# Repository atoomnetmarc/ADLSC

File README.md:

# ADLSC, Atoomnet's Digital Led String Controller

ESP32 based 5V digital LED controller build for use with [WLED](https://kno.wled.ge/).

# Design choices

The chosen ESP32 classic is the ESP32-WROVER-E with PSRAM on a [ESP32-DevKitC V4 board](https://docs.espressif.com/projects/esp-idf/en/release-v4.2/esp32/hw-reference/esp32/get-started-devkitc.html).

The ESP32 must be able to control the power to the LEDs. That means a high-side power switch.

The ESP32 will be powered by the same 5V power supply. A 0.5A 1812 polyfuse with 5V bidirectional TVS diode will used to protect the low power electronics.

5V will be monitored by a MAX809M reset ic. When the power supply voltage is too low the ESP32 will be turned off and in turn the LEDs will be turned off.

A N-channel MOSFET (AOD442) will be used as a 5V reverse polarity protection.

The power to the LEDs can be injected in 2 sections. Both are fused by a 5x20mm slow blow glass fuse paired with 5V bidirectional TVS diodes (like SMBJ5.0CA). Red LEDs will be parallel connected to easily identify a blown fuse.

# BOM

See Kicad directory for PCB BOM.

PCB BOM Notes:

- Instead of [Weidmueller 1824810000 clamp terminals](https://catalog.weidmueller.com/catalog/Start.do?localeId=en&ObjectID=1824810000) you could also use [Weidmueller 1760520000](https://catalog.weidmueller.com/catalog/Start.do?localeId=en&ObjectID=1760520000) or [1760510000](https://catalog.weidmueller.com/catalog/Start.do?localeId=en_DE&ObjectID=1760510000) or generic 5.08mm pcb screw terminals.
- I made the fuse clip footprint to fit https://www.aliexpress.com/item/4000841928644.html, but other could also fit.

To complete the PCB you will also need:

- 2x 19pin 2.54mm pin header (possibly already included with the ESP32 board)
- 2x 19pin 2.54mm pin socket
- 1cm<sup>2</sup> of kapton tape

Then you will also need:

- Mean Well 5V 10A power supply: IRM-60-5ST
- 5V digital LED strip or matrix

# PCB assembly

Open the [Kicad interactive BOM](Kicad/bom/ibom.html). Use it to mark which component you have placed and soldered.

Recommended soldering order:

- Q2, Q4
- U2
- Q3
- U1
- D2, D6, D9, D10, D12
- D1, D3, D8, D11
- D4, D5, D7, D13
- D14
- Q1
- F1
- R5, R12, R16, R20
- R1, R3, R11, R22
- R21
- R2, R8, R10, R14, R15, R18, R19, R23
- C1, C3
- C2

Clean the top of the PCB.

Continue soldering:

- J1, J3, J4, J6
- A1, use the ESP32 module to align 2x19 pin socket.

Remove the ESP32 module.

Put a fuse in 2 fuse clips. Do this 2 times.\
Cover the bottom of the fuse clips with some kapton tape. This mechanically insulates the clips from the PCB.

Solder the fuse clips (with the fuses in it) into F2 and F3.

Remove fuses. Clean the bottom of the PCB.

# Testing

Set power supply max current to 0.1A. Connect power supply to J1. Slowly increase to 5V.\
You should notice less than 10mA current. D2 turns on.

Reverse the polarity of the power supply.\
D1 turns bright red. Current is about 10mA.

Restore polarity. Increase max current to 2A. Short C2, then turn on power supply.\
Polyfuse F1 will blow, supply current should significantly lower (to about 250mA), D3 will turn bright red.

# Firmware

While the ESP32 modules is not mounted to the PCB, [install `ESP32_WROVER.bin`](https://kno.wled.ge/basics/install-binary/).

Configure:
- WiFi
  - Network Name
  - A unique mDNS address
  - AP SSID and password
  - Disable WiFi sleep
- LED
  - Current limit to 5A
  - Output to the matrix you have
    - For a 80x8 matrix: WS281x, 55mA, GRB, 640 length
    - Data GPIO: 25
    - Relay GPIO: 4, invert.
    - Default brightness: 128
    - Brightness factor: 25%
- 2D configuration
   - Strip or panel: 2D Matrix
   - Number of panels: 1
   - Panel 0
     - 1<sup>st</sup> LED: Top Left
     - Orientation: Vertical
     - Serpentine
     - Dimensions: 80x8

# More testing

Connect ESP32 module to PCB. Set power supply current to 0.5A, 5V.\
Turn on power supply. Now observe:
- Current is about 150mA
- D2 green is on
- D6 green is on
- D9 green is on
- D12 green is on
- D8 red is on
- D11 red is on

Press and hold `EN` button of ESP32 module. All LEDs should turn off except D2 (and the onboard red led of the ESP32 module). Release `EN`.

Put fuses in F2 and F3. D8 and D11 will turn off, D6 and D12 will get brighter.\
Wait, did you turn off power supply while you put in the fuses?

Now really turn off power supply. Increase current to 5A.

Connect (part of) the LED matrix and start playing with WLED.

# Wiring

## High voltage

Consult an expert on how to wire mains voltage to the Mean Well 5V power supply.

## Low voltage

Suggestion: use black wire color for GND. Grey for 0V. Red for 5V. Blue for data.

When consulting https://en.wikipedia.org/wiki/American_wire_gauge you should:

- use AWG18 (0.75mm<sup>2</sup>) or thicker wiring to connect the 5V dc from the power supply using a red and grey wire to the 5V of the power supply
- use AWG20 (0.5mm<sup>2</sup>) or thicker wiring to connect 5V power to LED strip or matrix.

You may use any wire thickness (challenge accepted) to connect data1 (and data2) to the LED strip. Or use the same AWG20.

## Fuse rating for power supply

If you choose to use a different or lower amperage 5V power supply, then you must also use lower power glass fuses. Reserve 1A for the low power components (like the ESP32) then divide by 3 for the fuse rating. For a 10A power supply: (10A - 1A) / 3 = 3A fuse. Also make sure the power supply can handle short circuits by switching off or go into hiccup mode.

# ESP32 pins

| Name     | ESP32 pin | Usage                               |
| -------- | --------- | ----------------------------------- |
| DATA1    | IO25      | LED data                            |
| DATA2    | IO26      | LED clock or data for second string |
| POWER_ON | IO4       | LED power relay                     |
| SDA      | IO21      | I2C data                            |
| SCL      | IO22      | I2C clock                           |
| CS0      | IO4       | SPI chip select 0                   |
| CLK      | IO18      | SPI clock                           |
| MISO     | IO19      | SPI data in                         |
| MOSI     | IO23      | SPI data out                        |

# Expansion PMOD connectors

You could add you own custom functionality using the I2C and SPI PMOD connectors. Consult the schematic on what extra components you should solder to the PCB. These components are excluded from the BOM.

Note: the 3V3 on the I2C and SPI PMOD connectors come from the ESP32 3V3 regulator, keep current usage below 100mA.

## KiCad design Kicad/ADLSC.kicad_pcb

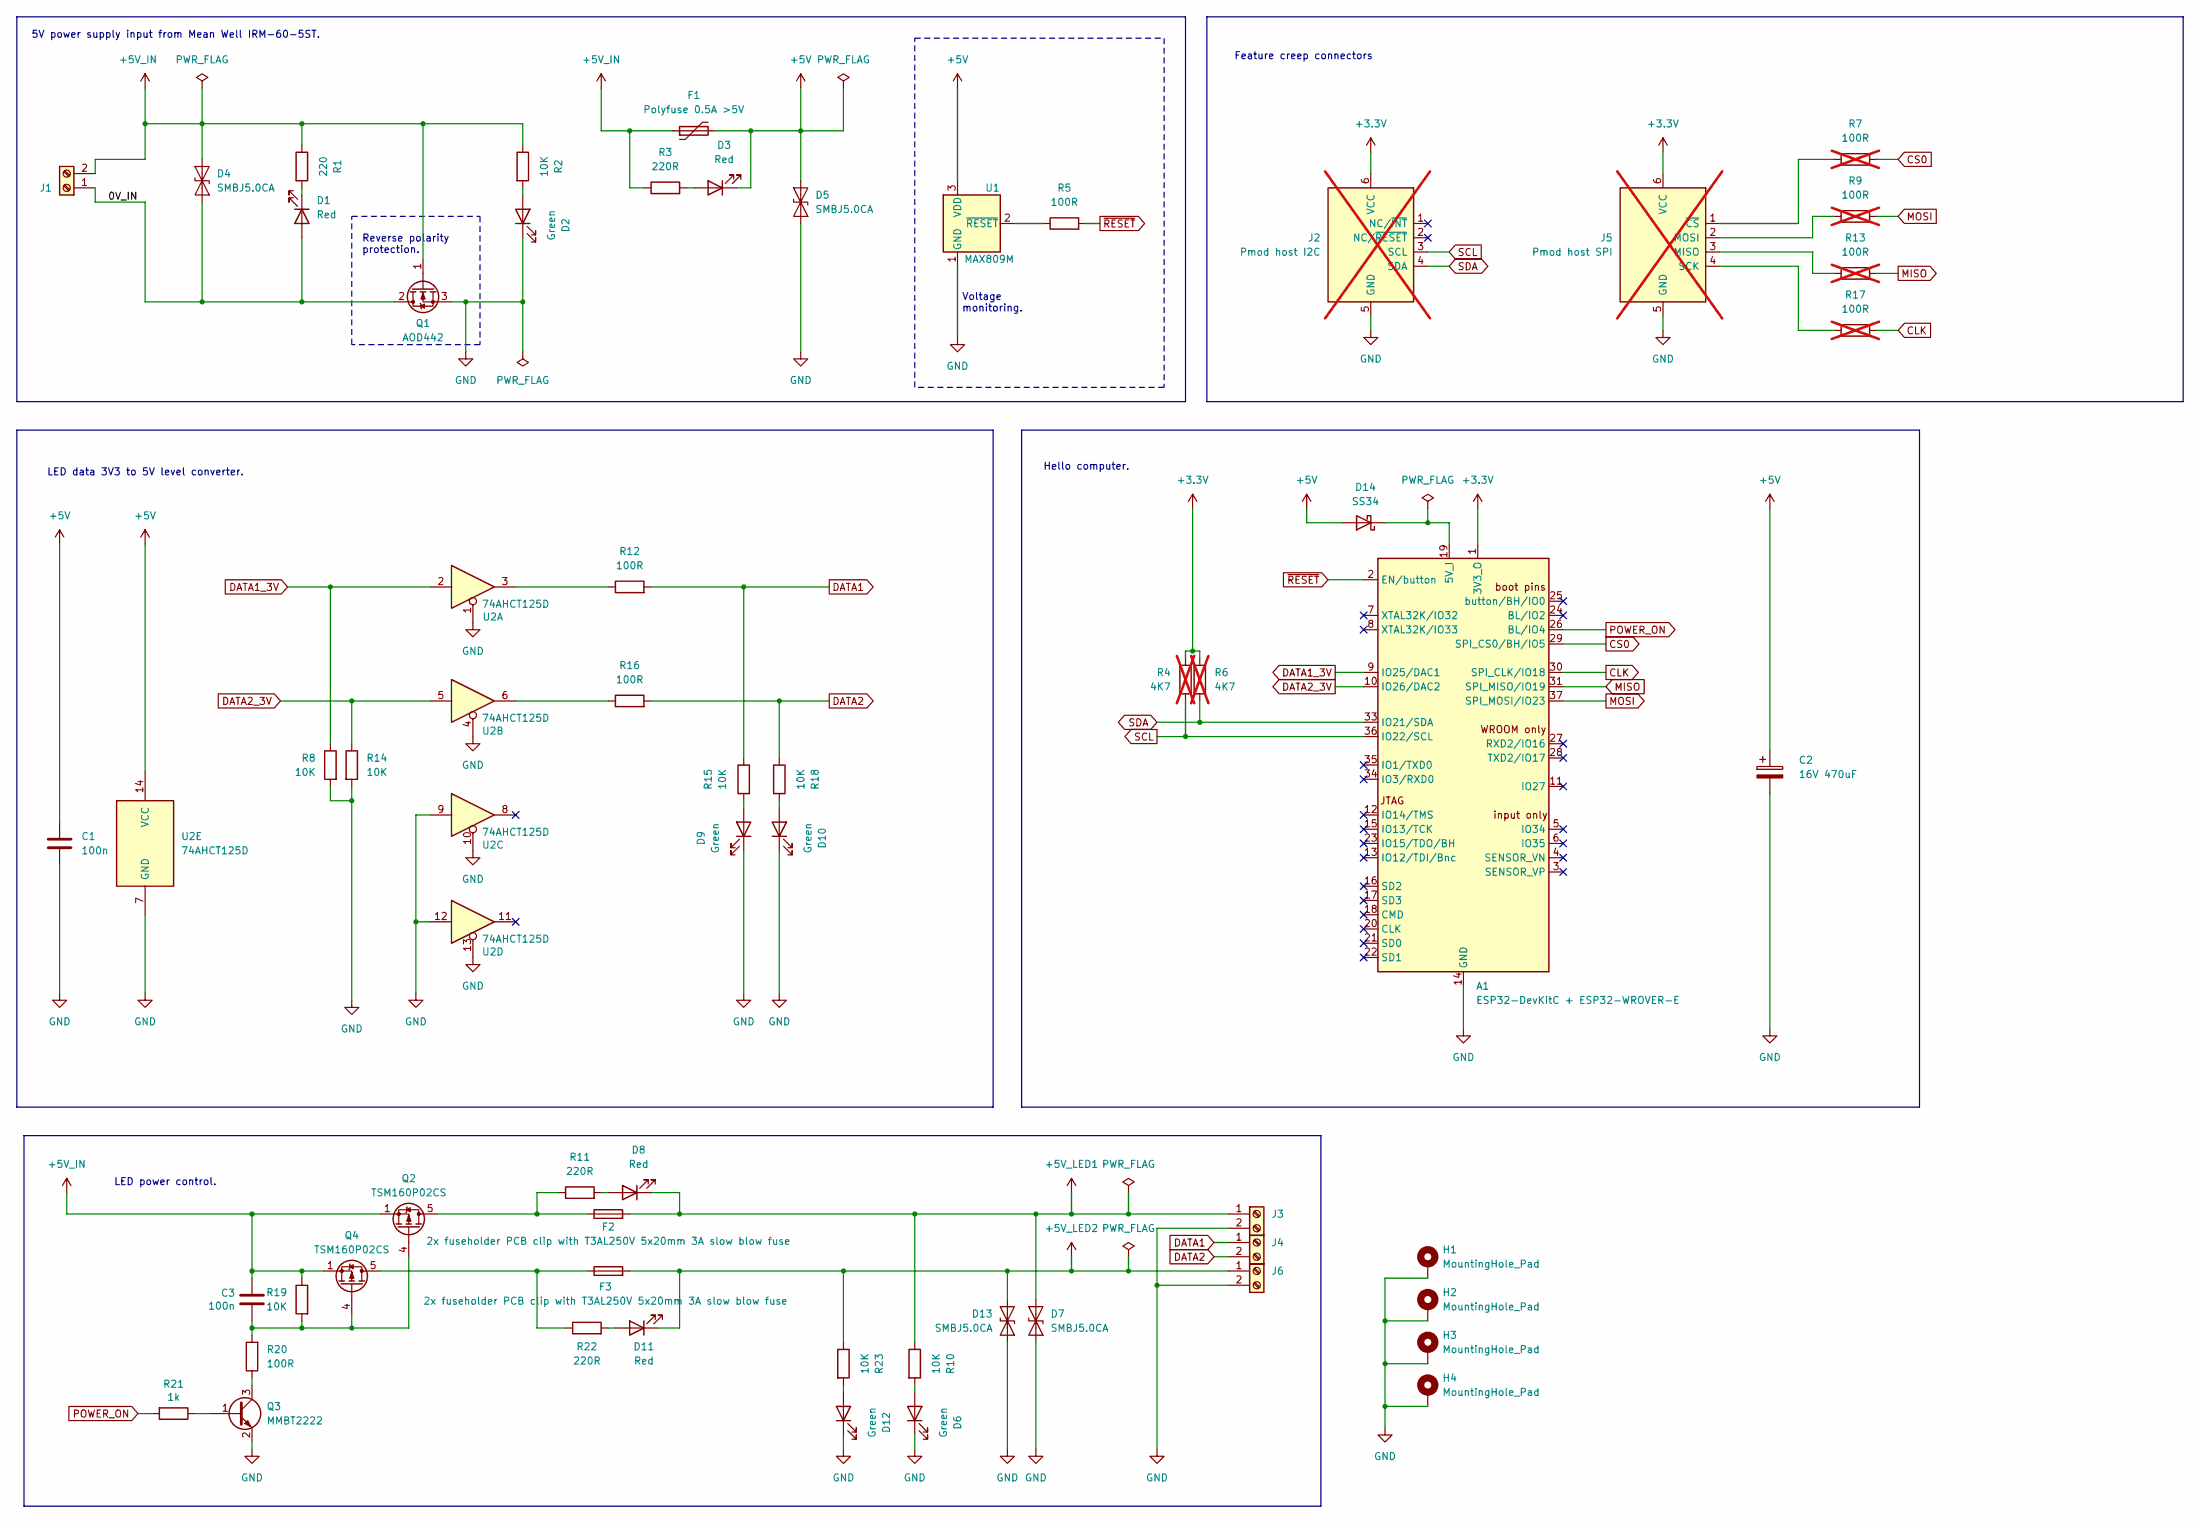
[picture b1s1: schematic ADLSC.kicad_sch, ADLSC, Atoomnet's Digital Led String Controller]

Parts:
A1: ESP32-DevKitC + ESP32-WROVER-E; ESP32-DevKitC
C1, C3: 100n; C_0805_2012Metric_Pad1.18x1.45mm_HandSolder
C2: 16V 470uF; CP_Elec_10x10.5
D1, D3, D8, D11: Red; LED_0805_2012Metric_Pad1.15x1.40mm_HandSolder
D2, D6, D9, D10, D12: Green; LED_0805_2012Metric_Pad1.15x1.40mm_HandSolder
D4, D5, D7, D13: SMBJ5.0CA; D_SMA
D14: SS34; D_SMA
F1: Polyfuse 0.5A >5V; Fuse_1812_4532Metric_Pad1.30x3.40mm_HandSolder
F2, F3: 2x fuseholder PCB clip with T3AL250V 5x20mm 3A sl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; Fuseholder_Clip-5x20mm_Inline_P20.50x4.60mm_Horizontal
H1, H2, H3, H4: MountingHole_Pad; MountingHole_3.2mm_M3_Pad_Via
J1, J3, J4, J6: Weidmueller 1824810000 or 1760520000; TerminalBlock_Weidmueller-PM-LSF-SMT-5.08-02-90-3.5SN-BK
J2: Pmod host I2C; PinSocket_1x06_P2.54mm_Horizontal; not fitted
J5: Pmod host SPI; PinSocket_1x06_P2.54mm_Horizontal; not fitted
Q1: AOD442; TO-252-2
Q2, Q4: TSM160P02CS; SOIC-8_3.9x4.9mm_P1.27mm
Q3: MMBT2222; SOT-23
R1: 220; R_0805_2012Metric_Pad1.20x1.40mm_HandSolder
R2, R8, R10, R14, R15, R18, R19, R23: 10K; R_0805_2012Metric_Pad1.20x1.40mm_HandSolder
R3, R11, R22: 220R; R_0805_2012Metric_Pad1.20x1.40mm_HandSolder
R4, R6: 4K7; R_0805_2012Metric_Pad1.20x1.40mm_HandSolder; not fitted
R5, R12, R16, R20: 100R; R_0805_2012Metric_Pad1.20x1.40mm_HandSolder
R7, R9, R13, R17: 100R; R_0805_2012Metric_Pad1.20x1.40mm_HandSolder; not fitted
R21: 1k; R_0805_2012Metric_Pad1.20x1.40mm_HandSolder
U1: MAX809M; SOT-23
U2: 74AHCT125D; SOIC-14_3.9x8.7mm_P1.27mm

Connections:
+3.3V: A1.1 (3V3_O), J2.6 (VCC), J5.6 (VCC), R4.2, R6.2
+5V: C1.1, C2.1, D3.1 (K), D5.2 (A2), D14.2 (A), F1.2, U1.3 (VDD), U2.14 (VCC)
+5V_IN: C3.1, D4.1 (A1), F1.1, J1.2, Q1.1 (G), Q2.1 (S), Q2.2 (S), Q2.3 (S), Q4.1 (S), Q4.2 (S), Q4.3 (S), R1.1, R2.1, R3.1, R19.1
+5V_LED1: D7.2 (A2), D8.1 (K), F2.2, J3.1, R10.1
+5V_LED2: D11.1 (K), D13.2 (A2), F3.2, J6.1, R23.1
/0V_IN: D1.2 (A), D4.2 (A2), J1.1, Q1.2 (D)
CLK: A1.30 (SPI_CLK/IO18), R17.2
CS0: A1.29 (SPI_CS0/BH/IO5), R7.2
DATA1: J4.1, R12.2, R15.1
DATA1_3V: A1.9 (IO25/DAC1), R8.1, U2.2
DATA2: J4.2, R16.2, R18.1
DATA2_3V: A1.10 (IO26/DAC2), R14.1, U2.5
GND: A1.14 (GND), A1.32 (GND), A1.38 (GND), C1.2, C2.2, D2.1 (K), D5.1 (A1), D6.1 (K), D7.1 (A1), D9.1 (K), D10.1 (K), D12.1 (K), D13.1 (A1), H1.1, H2.1, H3.1, H4.1, J2.5 (GND), J3.2, J5.5 (GND), J6.2, Q1.3 (S), Q3.2 (E), R8.2, R14.2, U1.1 (GND), U2.1, U2.4, U2.7 (GND), U2.9, U2.10, U2.12, U2.13
MISO: A1.31 (SPI_MISO/IO19), R13.2
MOSI: A1.37 (SPI_MOSI/IO23), R9.2
unnamed: A1.19 (5V_I), D14.1 (K)
unnamed: D1.1 (K), R1.2
unnamed: D2.2 (A), R2.2
unnamed: D3.2 (A), R3.2
unnamed: D6.2 (A), R10.2
unnamed: D8.2 (A), R11.2
unnamed: D9.2 (A), R15.2
unnamed: D10.2 (A), R18.2
unnamed: D11.2 (A), R22.2
unnamed: D12.2 (A), R23.2
unnamed: F2.1, Q2.5 (D), Q2.6 (D), Q2.7 (D), Q2.8 (D), R11.1
unnamed: F3.1, Q4.5 (D), Q4.6 (D), Q4.7 (D), Q4.8 (D), R22.1
unnamed: J5.3 (MISO), R13.1
unnamed: J5.2 (MOSI), R9.1
unnamed: J5.4 (SCK), R17.1
unnamed: J5.1 (~CS), R7.1
unnamed: C3.2, Q2.4 (G), Q4.4 (G), R19.2, R20.2
unnamed: Q3.1 (B), R21.1
unnamed: Q3.3 (C), R20.1
unnamed: R12.1, U2.3
unnamed: R16.1, U2.6
unnamed: R5.1, U1.2 (~RESET)
POWER_ON: A1.26 (BL/IO4), R21.2
SCL: A1.36 (IO22/SCL), J2.3 (SCL), R4.1
SDA: A1.33 (IO21/SDA), J2.4 (SDA), R6.1
~RESET: A1.2 (EN/button), R5.2

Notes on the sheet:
Voltage monitoring.
LED power control.
5V power supply input from Mean Well IRM-60-5ST.
LED data 3V3 to 5V level converter.
Reverse polarity protection.
Feature creep connectors
Hello computer.

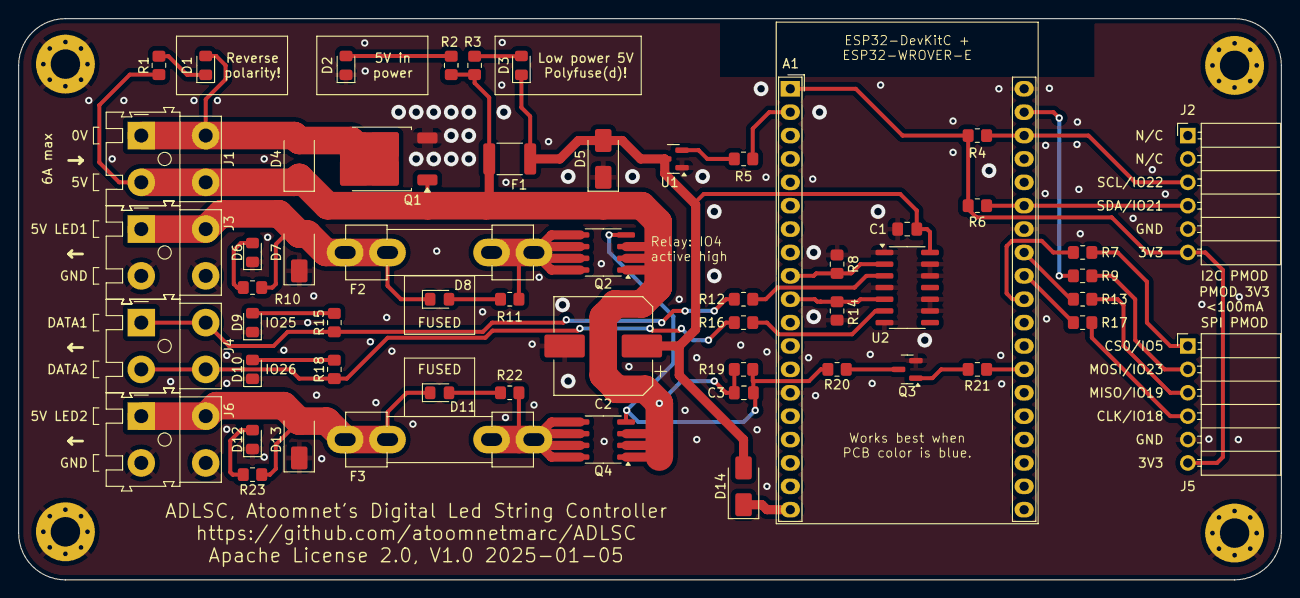
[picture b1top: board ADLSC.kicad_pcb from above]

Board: 2 copper layers, 137.2 x 61.0 mm, 60 parts (0 on the bottom side), 41 nets.

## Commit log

2024-12-13 Initial commit.
2024-12-13 progress
2025-01-04 Route PCB.
2025-01-05 Finalize pcb. Add gerbers. Add more readme.
2025-01-05 Remove do-not-place components from BOM.
2025-01-17 Assembly instructions.
2025-01-17 Pics or did not happen.
2025-01-17 Add missing config.

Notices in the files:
Kicad/ADLSC.kicad_pcb:
Apache License 2.0
README.md:
License: Apache 2.0
